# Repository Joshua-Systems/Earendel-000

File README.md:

# Earendel-000
PCB and Schematic design of the first star in the Nebula.

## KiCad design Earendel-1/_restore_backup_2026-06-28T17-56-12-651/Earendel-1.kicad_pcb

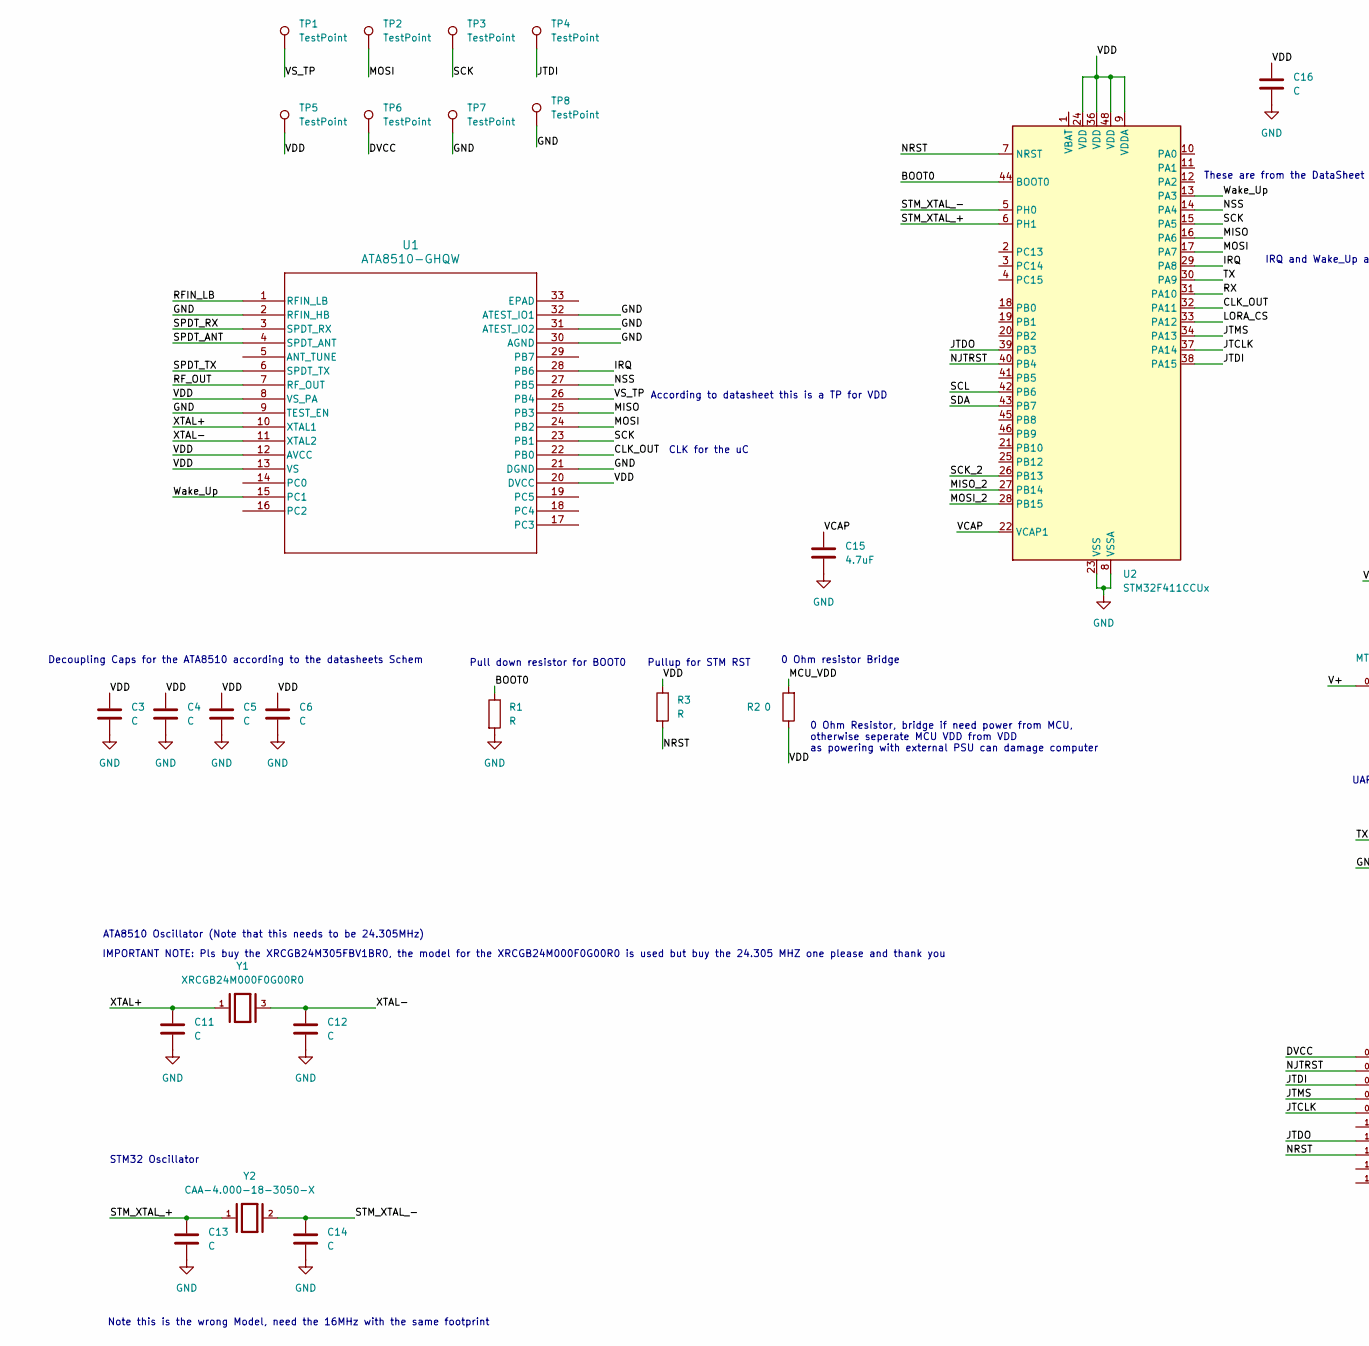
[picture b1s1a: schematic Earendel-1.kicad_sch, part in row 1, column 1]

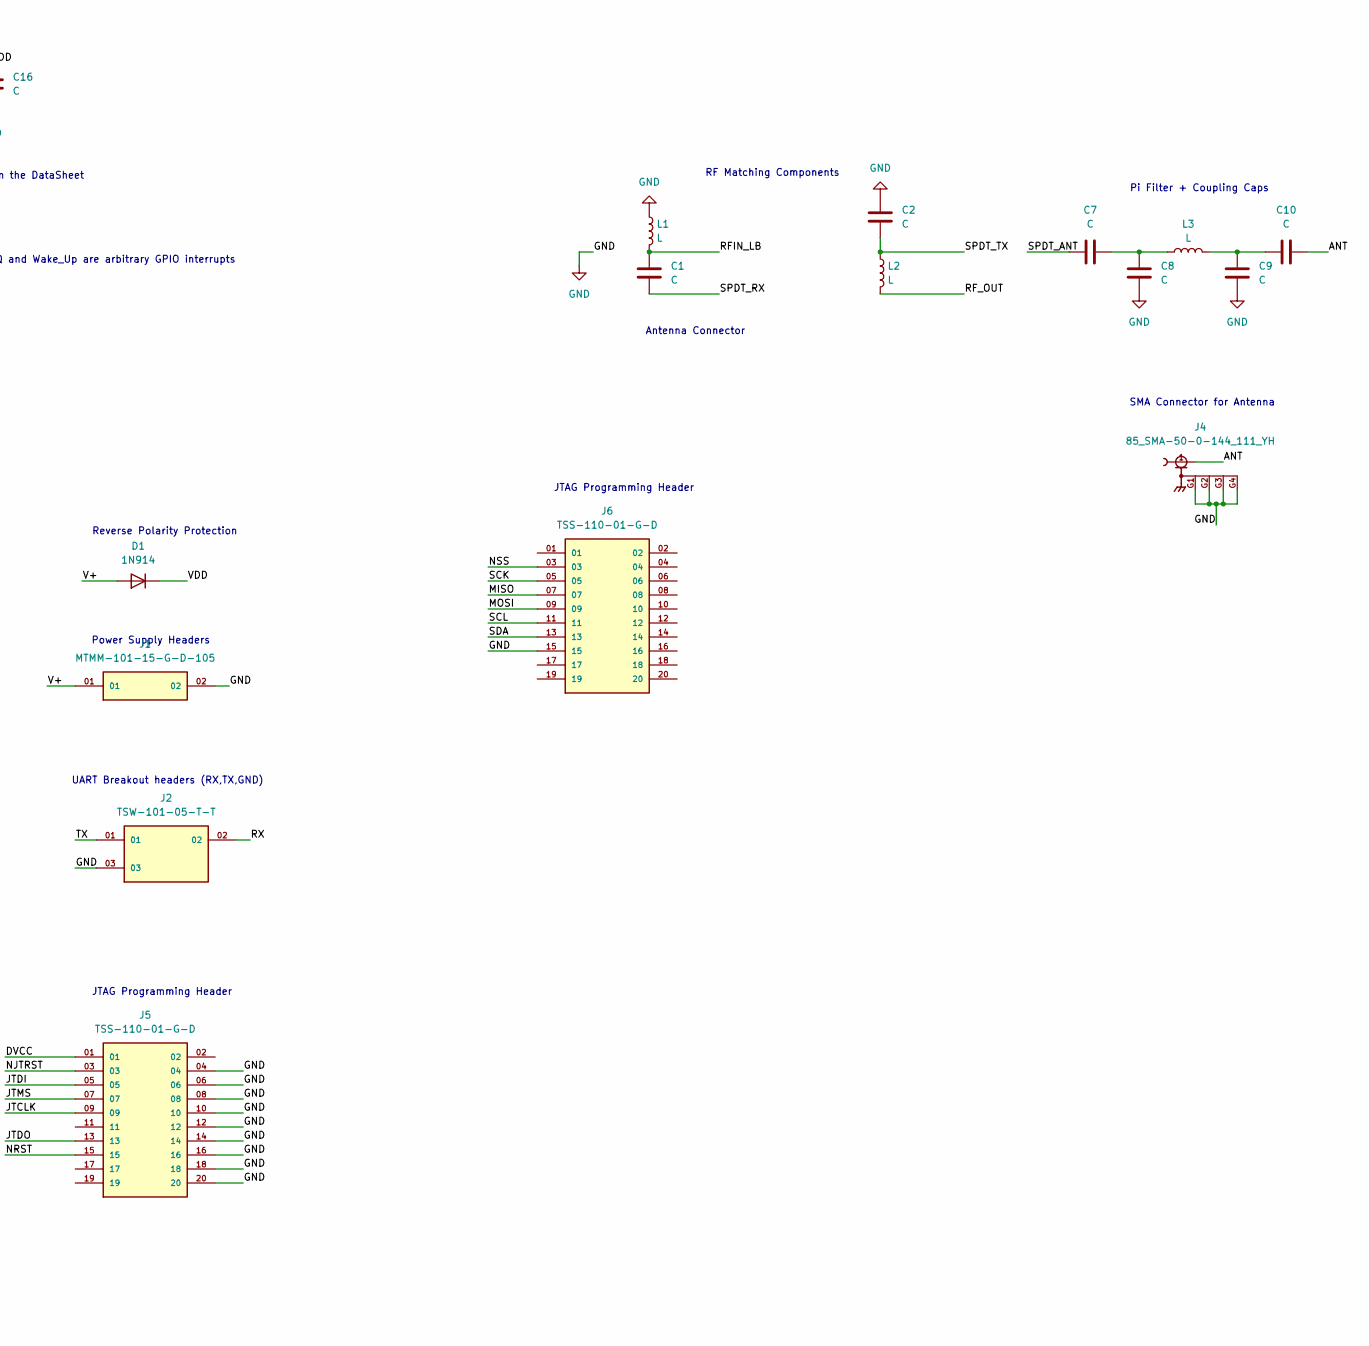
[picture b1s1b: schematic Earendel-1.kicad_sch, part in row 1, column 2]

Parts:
C1, C2, C3, C4, C5, C6, C7, C8, C9, C10, C11, C12, C13, C14, C16: C; C_0805_2012Metric_Pad1.18x1.45mm_HandSolder
C15: 4.7uF; C_0805_2012Metric_Pad1.18x1.45mm_HandSolder
D1: 1N914; D_DO-35_SOD27_P7.62mm_Horizontal
J1: MTMM-101-15-G-D-105; SAMTEC_MTMM-101-15-G-D-105
J2: TSW-101-05-T-T; SAMTEC_TSW-101-05-T-T; PARTREV R
J4: 85_SMA-50-0-144_111_YH; HUBER_SUHNER_85_SMA-50-0-144_111_YH; PARTREV a
J5, J6: TSS-110-01-G-D; SAMTEC_TSS-110-01-G-D; PARTREV R
L1, L2, L3: L; L_0805_2012Metric_Pad1.05x1.20mm_HandSolder
R1, R3: R; R_0805_2012Metric_Pad1.20x1.40mm_HandSolder
R2: 0; R_0805_2012Metric_Pad1.20x1.40mm_HandSolder
TP1: TestPoint; Pin_D0.7mm_L6.5mm_W1.8mm_FlatFork
TP2, TP3, TP4, TP5, TP6, TP7, TP8: TestPoint; Pin_D0.9mm_L10.0mm_W2.4mm_FlatFork
U1: ATA8510-GHQW; QFN50P500X500X100-33N
U2: STM32F411CCUx; QFN-48-1EP_7x7mm_P0.5mm_EP5.6x5.6mm
Y1: XRCGB24M000F0G00R0; OSC_XRCGB24M000F0G00R0; PARTREV N/A
Y2: CAA-4.000-18-3050-X; XTAL_CAA-4.000-18-3050-X-R; PARTREV August 01, 2022

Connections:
/ANT: C10.2, J4.1
/BOOT0: R1.1, U2.44 (BOOT0)
/CLK_OUT: U1.22 (PB0), U2.32 (PA11)
/DVCC: J5.01, TP6.1 (1_1)
/IRQ: U1.28 (PB6), U2.29 (PA8)
/JTCLK: J5.09, U2.37 (PA14)
/JTDI: J5.05, TP4.1 (1_1), U2.38 (PA15)
/JTDO: J5.13, U2.39 (PB3)
/JTMS: J5.07, U2.34 (PA13)
/LORA_CS: U2.33 (PA12)
/MCU_VDD: R2.2
/MISO: J6.07, U1.25 (PB3), U2.16 (PA6)
/MISO_2: U2.27 (PB14)
/MOSI: J6.09, TP2.1 (1_1), U1.24 (PB2), U2.17 (PA7)
/MOSI_2: U2.28 (PB15)
/NJTRST: J5.03, U2.40 (PB4)
/NRST: J5.15, R3.2, U2.7 (NRST)
/NSS: J6.03, U1.27 (PB5), U2.14 (PA4)
/RFIN_LB: C1.1, L1.2, U1.1 (RFIN_LB)
/RF_OUT: L2.2, U1.7 (RF_OUT)
/RX: J2.02, U2.31 (PA10)
/SCK: J6.05, TP3.1 (1_1), U1.23 (PB1), U2.15 (PA5)
/SCK_2: U2.26 (PB13)
/SCL: J6.11, U2.42 (PB6)
/SDA: J6.13, U2.43 (PB7)
/SPDT_ANT: C7.1, U1.4 (SPDT_ANT)
/SPDT_RX: C1.2, U1.3 (SPDT_RX)
/SPDT_TX: C2.2, L2.1, U1.6 (SPDT_TX)
/STM_XTAL_+: C13.1, U2.6 (PH1), Y2.1
/STM_XTAL_-: C14.1, U2.5 (PH0), Y2.2
/TX: J2.01, U2.30 (PA9)
/V+: D1.2 (A), J1.01
/VCAP: C15.1, U2.22 (VCAP1)
/VDD: C3.1, C4.1, C5.1, C6.1, C16.1, D1.1 (K), R2.1, R3.1, TP5.1 (1_1), U1.8 (VS_PA), U1.12 (AVCC), U1.13 (VS), U1.20 (DVCC), U2.9 (VDDA), U2.24 (VDD), U2.36 (VDD), U2.48 (VDD)
/VS_TP: TP1.1 (1_1), U1.26 (PB4)
/Wake_Up: U1.15 (PC1), U2.13 (PA3)
/XTAL+: C11.1, U1.10 (XTAL1), Y1.1
/XTAL-: C12.1, U1.11 (XTAL2), Y1.3
GND: C2.1, C3.2, C4.2, C5.2, C6.2, C8.2, C9.2, C11.2, C12.2, C13.2, C14.2, C15.2, C16.2, J1.02, J2.03, J4.G1, J4.G2, J4.G3, J4.G4, J5.04, J5.06, J5.08, J5.10, J5.12, J5.14, J5.16, J5.18, J5.20, J6.15, L1.1, R1.2, TP7.1 (1_1), TP8.1 (1_1), U1.2 (RFIN_HB), U1.9 (TEST_EN), U1.21 (DGND), U1.30 (AGND), U1.31 (ATEST_IO2), U1.32 (ATEST_IO1), U2.8 (VSSA), U2.23 (VSS), U2.35 (VSS), U2.47 (VSS), U2.49 (VSS)
unnamed: C7.2, C8.1, L3.1
unnamed: C9.1, C10.1, L3.2

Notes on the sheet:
According to datasheet this is a TP for VDD
RF Matching Components
0 Ohm resistor Bridge
Pull down resistor for BOOT0
UART Breakout headers (RX,TX,GND)
These are from the DataSheet
Antenna Connector
Pullup for STM RST
Power Supply Headers
Note this is the wrong Model, need the 16MHz with the same footprint
Decoupling Caps for the ATA8510 according to the datasheets Schem
CLK for the uC
0 Ohm Resistor, bridge if need power from MCU, otherwise seperate MCU VDD from VDD as powering with external PSU can damage computer
STM32 Oscillator
JTAG Programming Header
IMPORTANT NOTE: Pls buy the XRCGB24M305FBV1BR0, the model for the XRCGB24M000F0G00R0 is used but buy the 24.305 MHZ one please and thank you
IRQ and Wake_Up are arbitrary GPIO interrupts
SMA Connector for Antenna
Pi Filter + Coupling Caps
ATA8510 Oscillator (Note that this needs to be 24.305MHz)
Reverse Polarity Protection

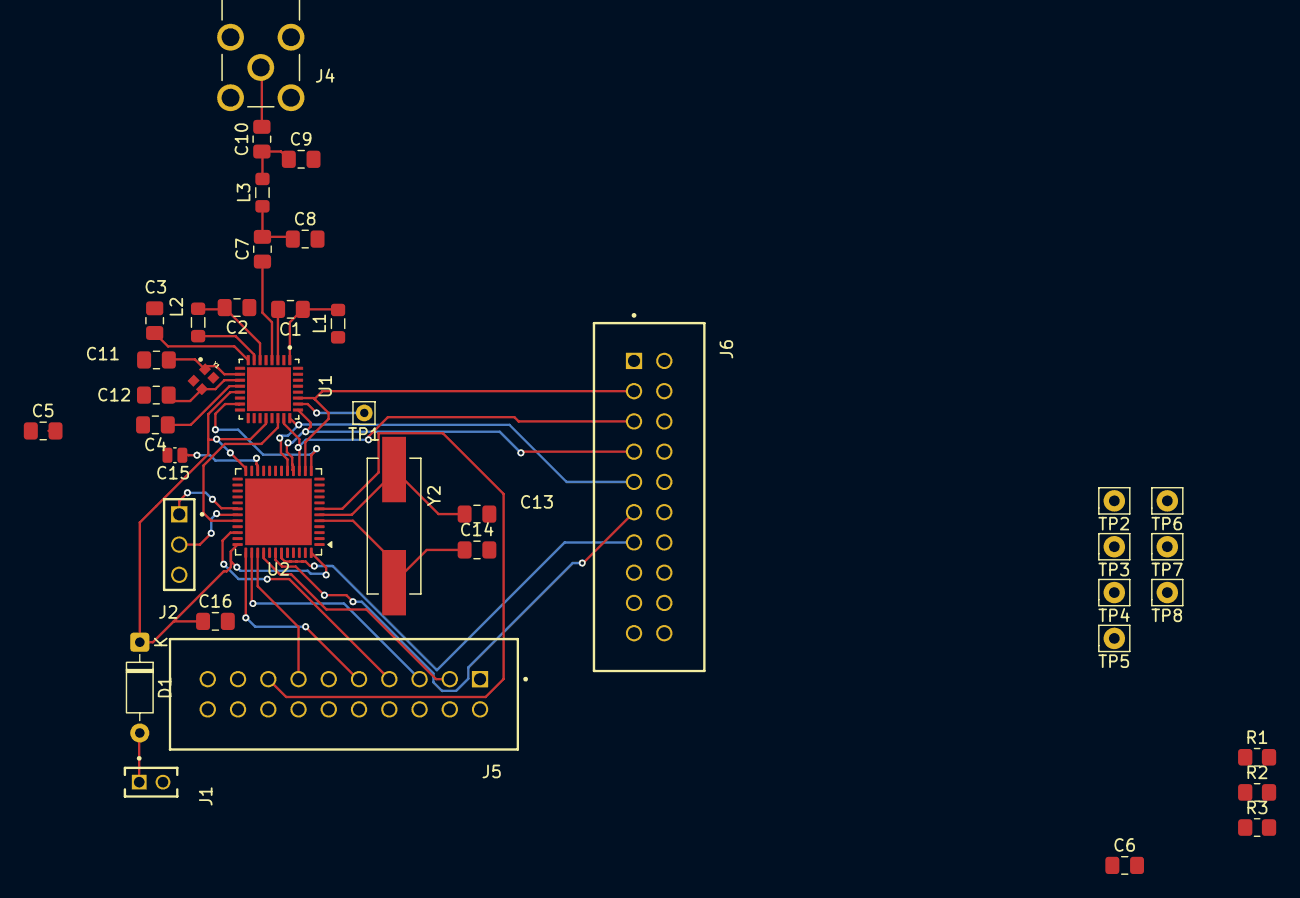
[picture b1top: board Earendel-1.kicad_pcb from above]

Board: 2 copper layers, 40 parts (0 on the bottom side), 36 nets.

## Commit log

2026-06-01 Initial Schematic SPI set up and library set up
2026-06-01 Updated RF input and output matching network
2026-06-03 Finished ATA-8510 Schem Items and filters
2026-06-08 JTAG header added
2026-06-09 UART + power headers to schematic
2026-06-10 New SMA connector
2026-06-26 Save State for PCB
2026-06-26 commiting new libraries
2026-06-26 first Routing
2026-06-26 Programmer and ATA mostly routed
2026-06-27 toying with traces
2026-06-28 Finished V0 PCB
